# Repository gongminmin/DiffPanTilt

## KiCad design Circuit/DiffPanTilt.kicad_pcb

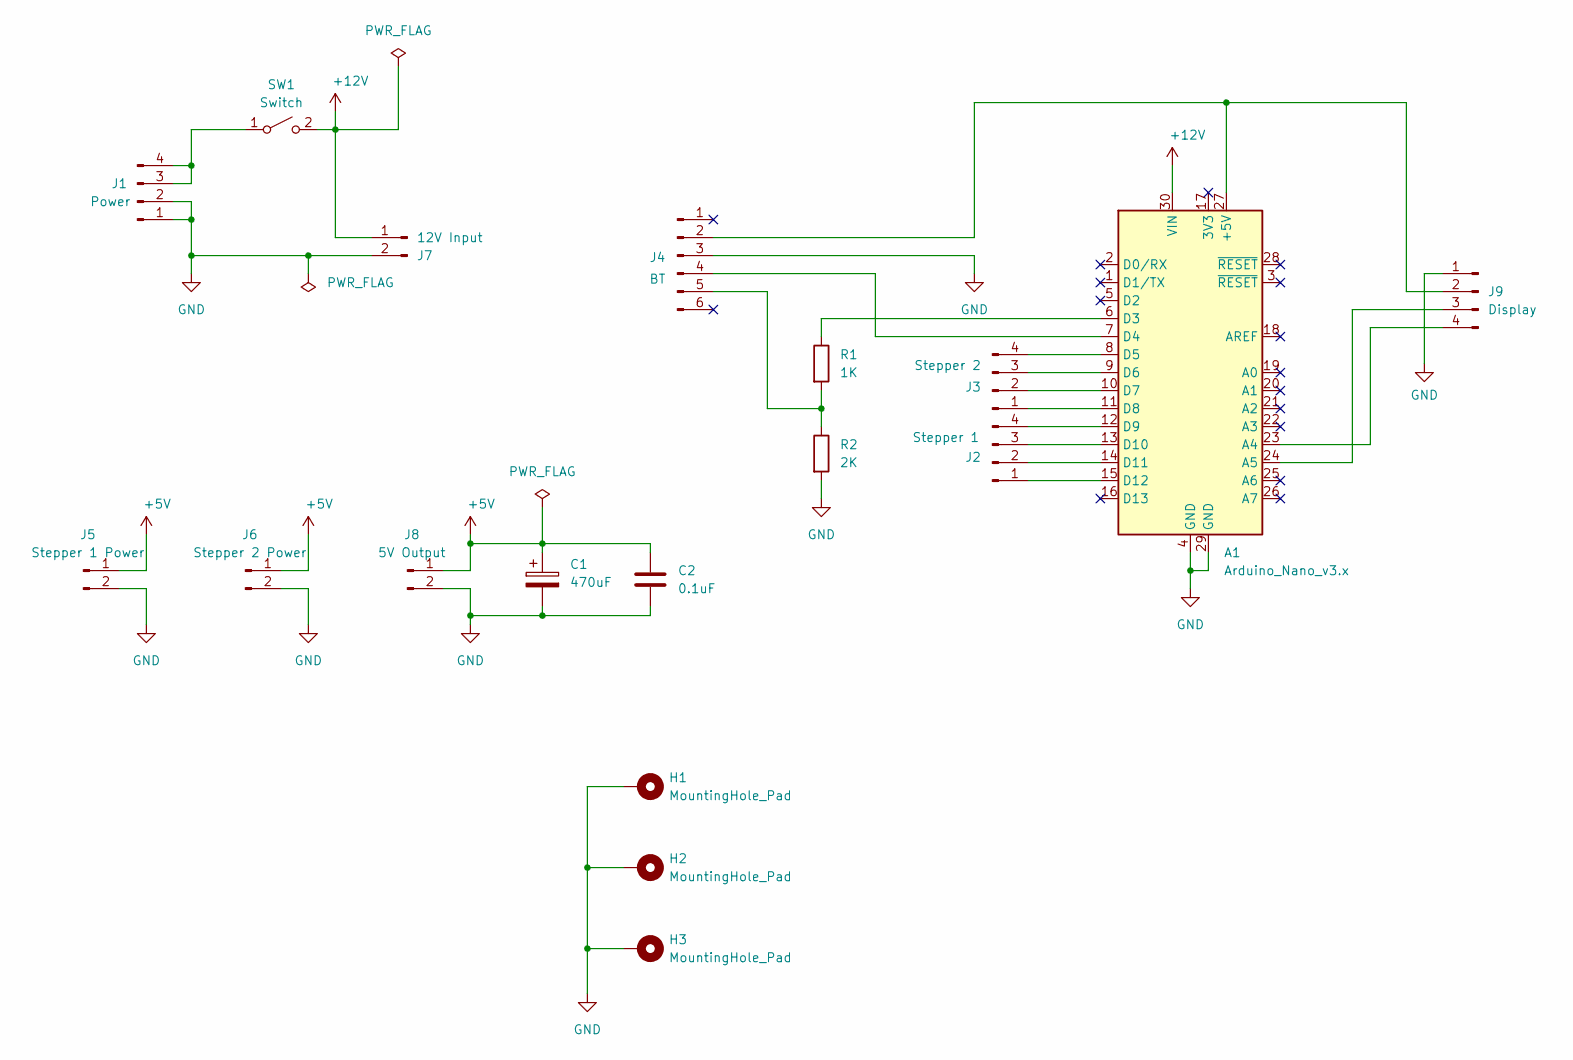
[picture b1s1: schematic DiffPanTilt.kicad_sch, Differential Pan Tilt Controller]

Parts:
A1: Arduino_Nano_v3.x; Arduino_Nano
C1: 470uF; CP_Radial_D12.5mm_P5.00mm
C2: 0.1uF; C_Rect_L4.6mm_W3.8mm_P2.50mm_MKS02_FKP02
H1, H2, H3: MountingHole_Pad; MountingHole_2.2mm_M2_Pad_Via
J1: Power; PinSocket_1x04_P2.54mm_Vertical
J2: Stepper 1; PinHeader_1x04_P2.54mm_Vertical
J3: Stepper 2; PinHeader_1x04_P2.54mm_Vertical
J4: BT; PinHeader_1x06_P2.54mm_Vertical
J5: Stepper 1 Power; PinHeader_1x02_P2.54mm_Vertical
J6: Stepper 2 Power; PinHeader_1x02_P2.54mm_Vertical
J7: 12V Input; PinHeader_1x02_P2.54mm_Vertical
J8: 5V Output; PinHeader_1x02_P2.54mm_Vertical
J9: Display; PinHeader_1x04_P2.54mm_Vertical
R1: 1K; R_Axial_DIN0207_L6.3mm_D2.5mm_P7.62mm_Horizontal
R2: 2K; R_Axial_DIN0207_L6.3mm_D2.5mm_P7.62mm_Horizontal
SW1: Switch; PinHeader_1x02_P2.54mm_Vertical

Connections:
+5V: C1.1, C2.1, J5.1, J6.1, J8.1
+12V: A1.30 (VIN), J7.1, SW1.2 (B)
GND: A1.4 (GND), A1.29 (GND), C1.2, C2.2, H1.1, H2.1, H3.1, J1.1, J1.2, J4.3, J5.2, J6.2, J7.2, J8.2, J9.1, R2.2
unnamed: A1.27 (+5V), J4.2, J9.2
unnamed: A1.23 (A4), J9.4
unnamed: A1.24 (A5), J9.3
unnamed: A1.6 (D3), R1.1
unnamed: A1.7 (D4), J4.4
unnamed: A1.8 (D5), J3.4
unnamed: A1.9 (D6), J3.3
unnamed: A1.10 (D7), J3.2
unnamed: A1.11 (D8), J3.1
unnamed: A1.12 (D9), J2.4
unnamed: A1.13 (D10), J2.3
unnamed: A1.14 (D11), J2.2
unnamed: A1.15 (D12), J2.1
unnamed: J1.3, J1.4, SW1.1 (A)
unnamed: J4.5, R1.2, R2.1

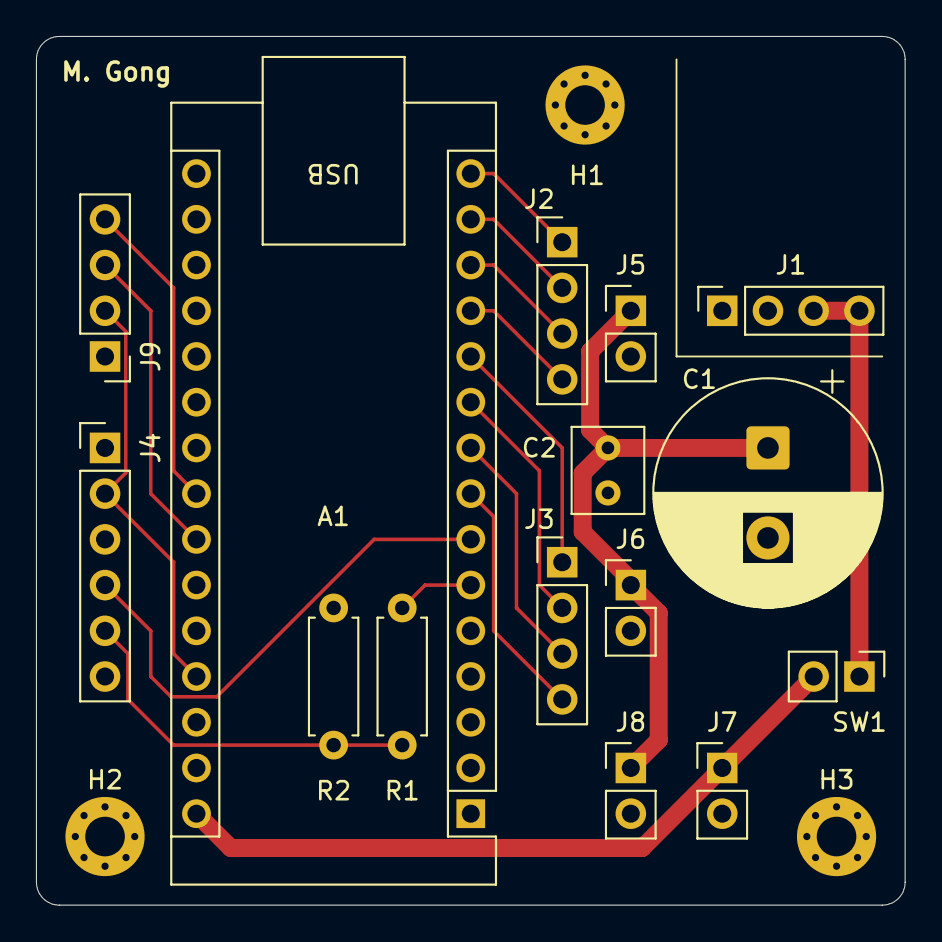
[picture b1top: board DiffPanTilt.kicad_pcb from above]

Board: 2 copper layers, 48.3 x 48.3 mm, 18 parts (0 on the bottom side), 18 nets.

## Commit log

2025-10-11 Initial checkin
2025-10-12 [3DModel] Add 3D printing models of some parts
2026-01-25 [Circuit] Add circuit and pcb design
2026-01-28 [3DModel] Add script for generating gears
2026-01-31 [Circuit] Change the footprint of J1 to pin socket, and fine tune the PCB layout
2026-02-02 [Circuit] Set *.kicad_pro to use LF as EOL
2026-02-02 [Circuit] Add `production` directory into ignore
